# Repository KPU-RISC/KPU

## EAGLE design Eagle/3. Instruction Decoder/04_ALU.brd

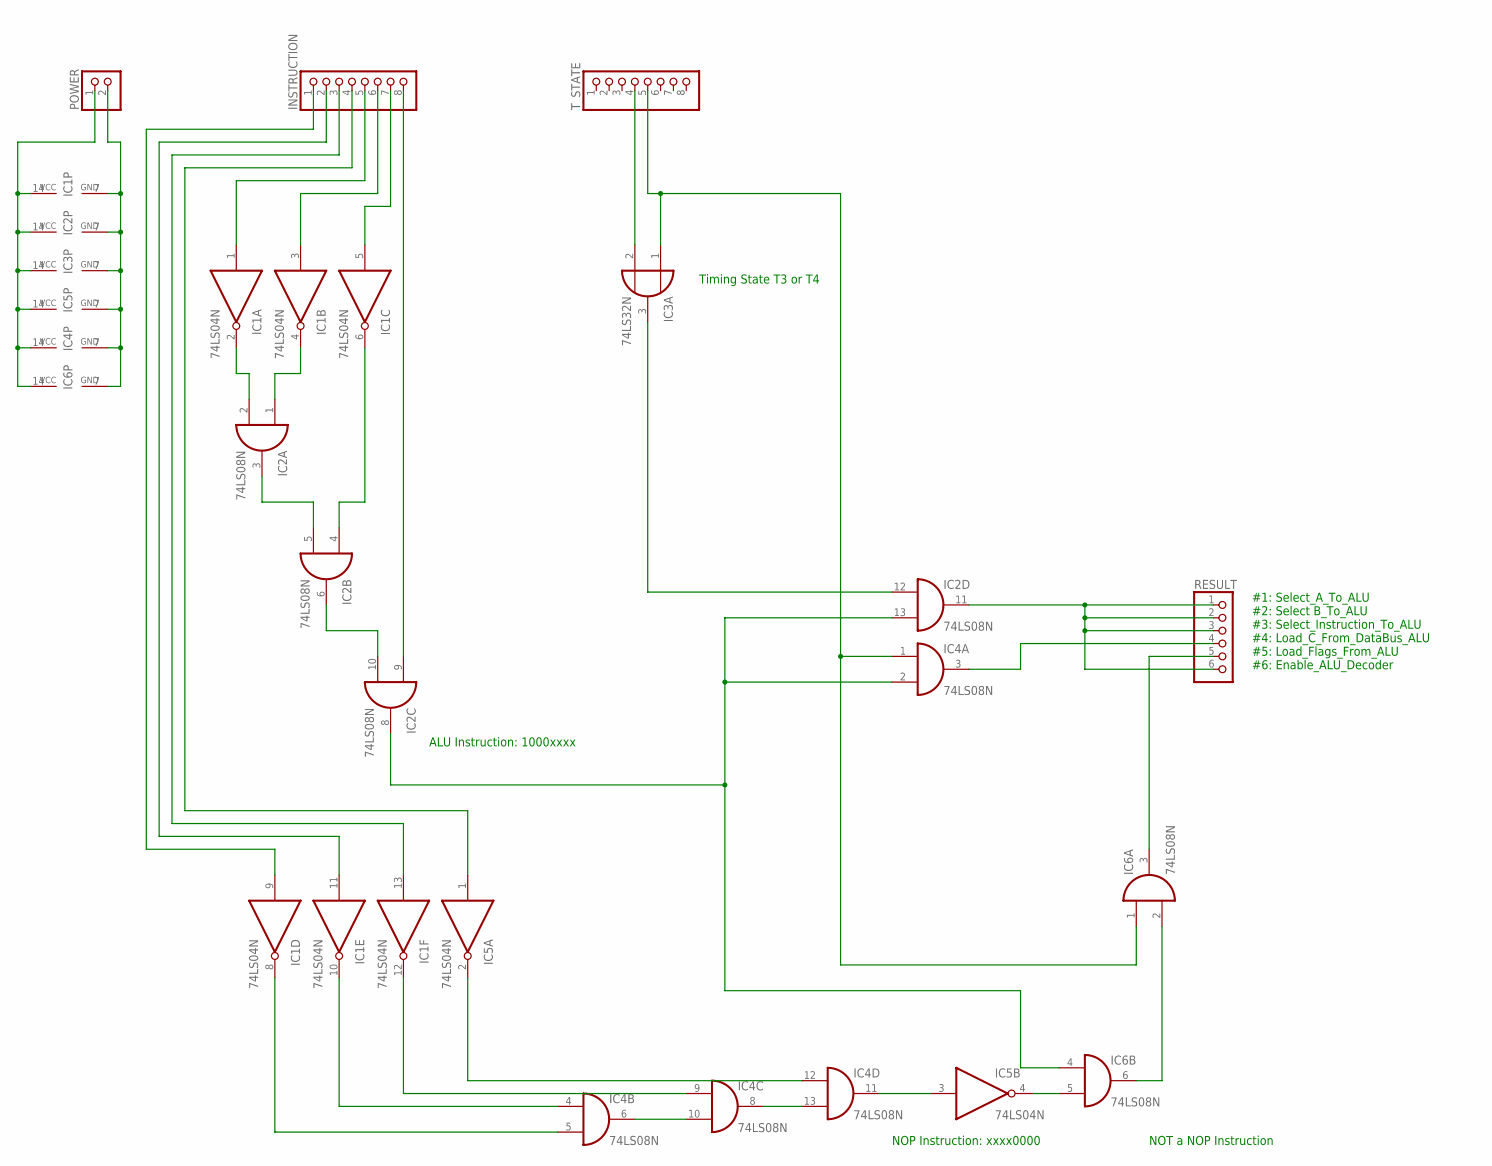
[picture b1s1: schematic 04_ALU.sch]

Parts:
IC1, IC5: 74LS04N; DIL14
IC2, IC4, IC6: 74LS08N; DIL14
IC3: 74LS32N; DIL14
INSTRUCTION: PINHD-1X8; 1X08
POWER: PINHD-1X2; 1X02
RESULT: PINHD-1X6; 1X06
T_STATE: PINHD-1X8; 1X08

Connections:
GND: IC1.7 (GND), IC2.7 (GND), IC3.7 (GND), IC4.7 (GND), IC5.7 (GND), IC6.7 (GND), POWER.2
unnamed: IC1.1 (I), INSTRUCTION.5
unnamed: IC1.3 (I), INSTRUCTION.6
unnamed: IC1.5 (I), INSTRUCTION.7
unnamed: IC1.2 (O), IC2.2 (I1)
unnamed: IC1.4 (O), IC2.1 (I0)
unnamed: IC2.3 (O), IC2.5 (I1)
unnamed: IC1.6 (O), IC2.4 (I0)
unnamed: IC2.9 (I0), INSTRUCTION.8
unnamed: IC2.6 (O), IC2.10 (I1)
unnamed: IC3.2 (I1), T_STATE.4
unnamed: IC3.1 (I0), IC4.1 (I0), IC6.1 (I0), T_STATE.5
unnamed: IC2.8 (O), IC2.13 (I1), IC4.2 (I1), IC6.4 (I0)
unnamed: IC2.12 (I0), IC3.3 (O)
unnamed: IC2.11 (O), RESULT.1, RESULT.2, RESULT.3, RESULT.6
unnamed: IC4.3 (O), RESULT.4
unnamed: IC1.9 (I), INSTRUCTION.1
unnamed: IC1.11 (I), INSTRUCTION.2
unnamed: IC1.13 (I), INSTRUCTION.3
unnamed: IC5.1 (I), INSTRUCTION.4
unnamed: IC1.8 (O), IC4.5 (I1)
unnamed: IC1.10 (O), IC4.4 (I0)
unnamed: IC4.6 (O), IC4.10 (I1)
unnamed: IC1.12 (O), IC4.9 (I0)
unnamed: IC4.8 (O), IC4.13 (I1)
unnamed: IC4.12 (I0), IC5.2 (O)
unnamed: IC4.11 (O), IC5.3 (I)
unnamed: IC5.4 (O), IC6.5 (I1)
unnamed: IC6.3 (O), RESULT.5
unnamed: IC6.2 (I1), IC6.6 (O)
VCC: IC1.14 (VCC), IC2.14 (VCC), IC3.14 (VCC), IC4.14 (VCC), IC5.14 (VCC), IC6.14 (VCC), POWER.1

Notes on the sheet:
ALU Instruction: 1000xxxx
Timing State T3 or T4
#1: Select_A_To_ALU #2: Select B_To_ALU #3: Select_Instruction_To_ALU #4: Load_C_From_DataBus_ALU #5: Load_Flags_From_ALU #6: Enable_ALU_Decoder
NOP Instruction: xxxx0000
NOT a NOP Instruction

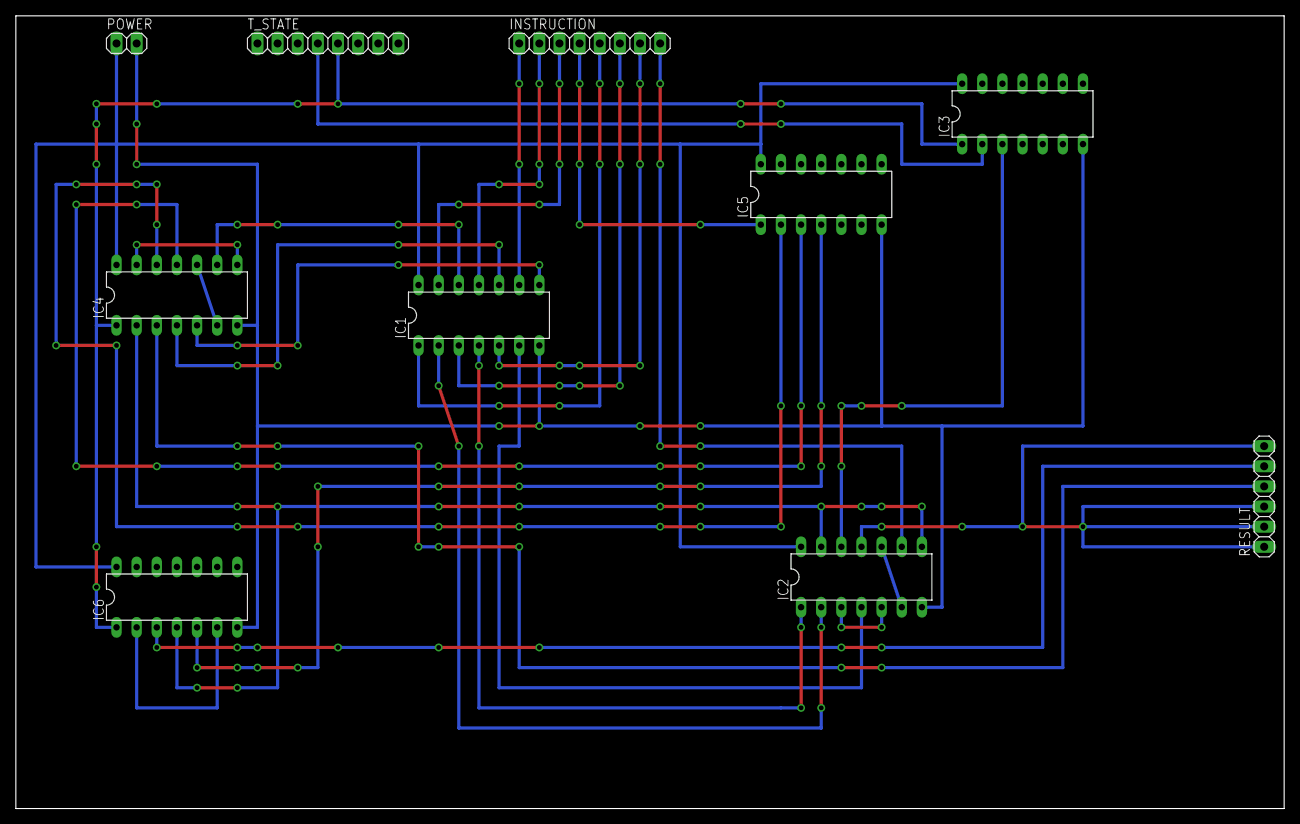
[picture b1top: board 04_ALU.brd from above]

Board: 2 copper layers, 160.0 x 100.0 mm, 10 parts (0 on the bottom side), 31 nets.

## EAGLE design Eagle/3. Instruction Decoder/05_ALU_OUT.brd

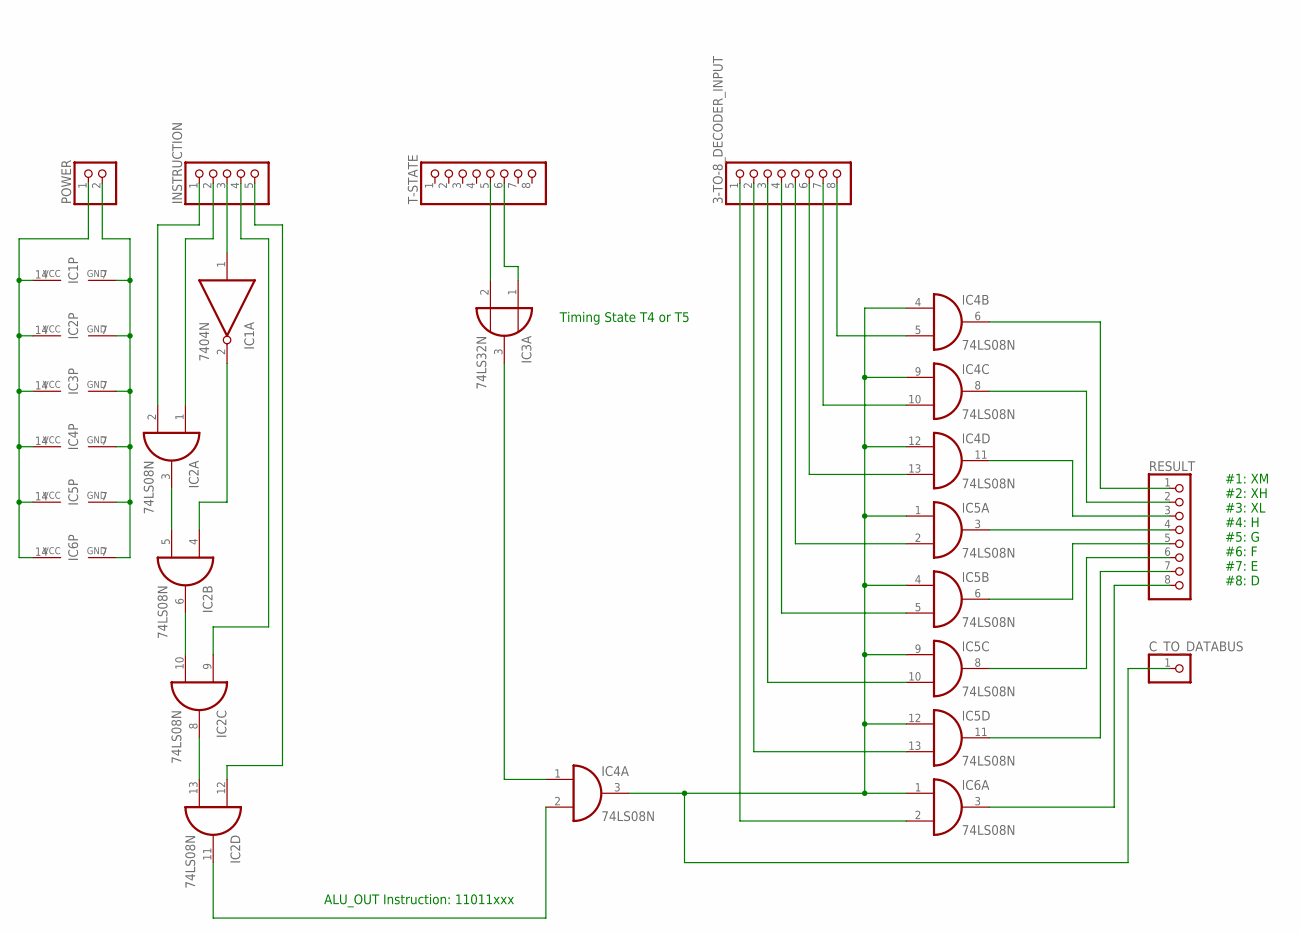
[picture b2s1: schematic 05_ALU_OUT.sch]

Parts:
3-TO-8_DECODER_INPUT: PINHD-1X8; 1X08
C_TO_DATABUS: PINHD-1X1; 1X01
IC1: 7404N; DIL14
IC2, IC4, IC5, IC6: 74LS08N; DIL14
IC3: 74LS32N; DIL14
INSTRUCTION: PINHD-1X5; 1X05
POWER: PINHD-1X2; 1X02
RESULT: PINHD-1X8; 1X08
T-STATE: PINHD-1X8; 1X08

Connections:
GND: IC1.7 (GND), IC2.7 (GND), IC3.7 (GND), IC4.7 (GND), IC5.7 (GND), IC6.7 (GND), POWER.2
unnamed: IC1.1 (I), INSTRUCTION.3
unnamed: IC2.2 (I1), INSTRUCTION.1
unnamed: IC2.1 (I0), INSTRUCTION.2
unnamed: IC2.3 (O), IC2.5 (I1)
unnamed: IC1.2 (O), IC2.4 (I0)
unnamed: IC2.6 (O), IC2.10 (I1)
unnamed: IC2.9 (I0), INSTRUCTION.4
unnamed: IC2.8 (O), IC2.13 (I1)
unnamed: IC2.12 (I0), INSTRUCTION.5
unnamed: IC2.11 (O), IC4.2 (I1)
unnamed: IC3.2 (I1), T-STATE.5
unnamed: IC3.1 (I0), T-STATE.6
unnamed: IC3.3 (O), IC4.1 (I0)
unnamed: C_TO_DATABUS.1, IC4.3 (O), IC4.4 (I0), IC4.9 (I0), IC4.12 (I0), IC5.1 (I0), IC5.4 (I0), IC5.9 (I0), IC5.12 (I0), IC6.1 (I0)
unnamed: 3-TO-8_DECODER_INPUT.8, IC4.5 (I1)
unnamed: 3-TO-8_DECODER_INPUT.7, IC4.10 (I1)
unnamed: 3-TO-8_DECODER_INPUT.6, IC4.13 (I1)
unnamed: 3-TO-8_DECODER_INPUT.5, IC5.2 (I1)
unnamed: 3-TO-8_DECODER_INPUT.4, IC5.5 (I1)
unnamed: 3-TO-8_DECODER_INPUT.3, IC5.10 (I1)
unnamed: 3-TO-8_DECODER_INPUT.2, IC5.13 (I1)
unnamed: 3-TO-8_DECODER_INPUT.1, IC6.2 (I1)
unnamed: IC4.6 (O), RESULT.1
unnamed: IC4.8 (O), RESULT.2
unnamed: IC4.11 (O), RESULT.3
unnamed: IC5.3 (O), RESULT.4
unnamed: IC5.6 (O), RESULT.5
unnamed: IC5.8 (O), RESULT.6
unnamed: IC5.11 (O), RESULT.7
unnamed: IC6.3 (O), RESULT.8
VCC: IC1.14 (VCC), IC2.14 (VCC), IC3.14 (VCC), IC4.14 (VCC), IC5.14 (VCC), IC6.14 (VCC), POWER.1

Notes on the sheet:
ALU_OUT Instruction: 11011xxx
Timing State T4 or T5
#1: XM #2: XH #3: XL #4: H #5: G #6: F #7: E #8: D

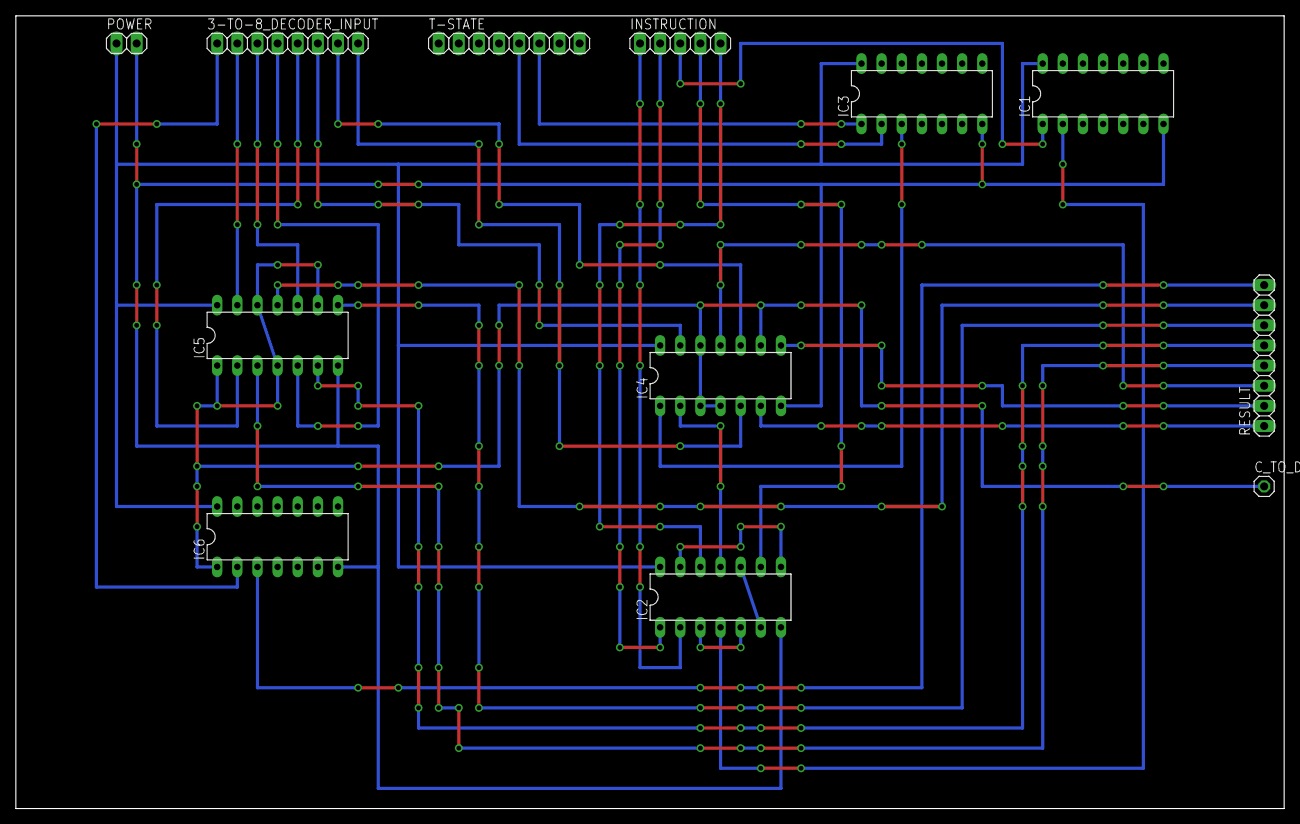
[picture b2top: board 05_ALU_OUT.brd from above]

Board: 2 copper layers, 160.0 x 100.0 mm, 12 parts (0 on the bottom side), 32 nets.

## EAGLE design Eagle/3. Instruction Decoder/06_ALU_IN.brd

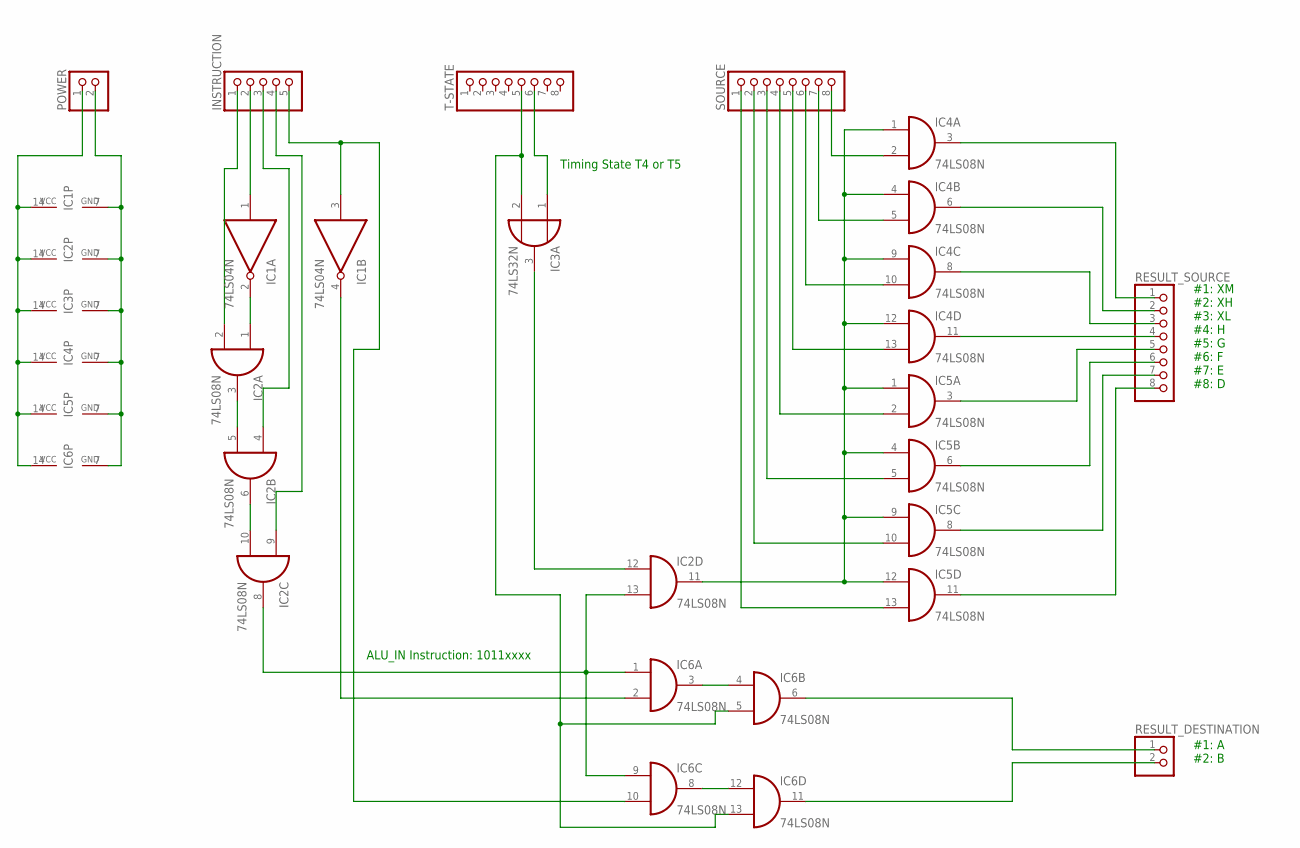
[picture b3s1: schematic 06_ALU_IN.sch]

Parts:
IC1: 74LS04N; DIL14
IC2, IC4, IC5, IC6: 74LS08N; DIL14
IC3: 74LS32N; DIL14
INSTRUCTION: PINHD-1X5; 1X05
POWER: PINHD-1X2; 1X02
RESULT_DESTINATION: PINHD-1X2; 1X02
RESULT_SOURCE: PINHD-1X8; 1X08
SOURCE: PINHD-1X8; 1X08
T-STATE: PINHD-1X8; 1X08

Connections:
GND: IC1.7 (GND), IC2.7 (GND), IC3.7 (GND), IC4.7 (GND), IC5.7 (GND), IC6.7 (GND), POWER.2
unnamed: IC1.1 (I), INSTRUCTION.2
unnamed: IC2.2 (I1), INSTRUCTION.1
unnamed: IC4.3 (O), RESULT_SOURCE.1
unnamed: IC1.2 (O), IC2.1 (I0)
unnamed: IC2.3 (O), IC2.5 (I1)
unnamed: IC2.4 (I0), INSTRUCTION.3
unnamed: IC2.6 (O), IC2.10 (I1)
unnamed: IC2.9 (I0), INSTRUCTION.4
unnamed: IC2.8 (O), IC2.13 (I1), IC6.1 (I0), IC6.9 (I0)
unnamed: IC3.2 (I1), IC6.5 (I1), IC6.13 (I1), T-STATE.5
unnamed: IC3.1 (I0), T-STATE.6
unnamed: IC2.12 (I0), IC3.3 (O)
unnamed: IC2.11 (O), IC4.1 (I0), IC4.4 (I0), IC4.9 (I0), IC4.12 (I0), IC5.1 (I0), IC5.4 (I0), IC5.9 (I0), IC5.12 (I0)
unnamed: IC5.13 (I1), SOURCE.1
unnamed: IC5.10 (I1), SOURCE.2
unnamed: IC5.5 (I1), SOURCE.3
unnamed: IC5.2 (I1), SOURCE.4
unnamed: IC4.13 (I1), SOURCE.5
unnamed: IC4.10 (I1), SOURCE.6
unnamed: IC4.5 (I1), SOURCE.7
unnamed: IC4.2 (I1), SOURCE.8
unnamed: IC4.6 (O), RESULT_SOURCE.2
unnamed: IC4.8 (O), RESULT_SOURCE.3
unnamed: IC4.11 (O), RESULT_SOURCE.4
unnamed: IC5.3 (O), RESULT_SOURCE.5
unnamed: IC5.6 (O), RESULT_SOURCE.6
unnamed: IC5.8 (O), RESULT_SOURCE.7
unnamed: IC5.11 (O), RESULT_SOURCE.8
unnamed: IC1.3 (I), IC6.10 (I1), INSTRUCTION.5
unnamed: IC1.4 (O), IC6.2 (I1)
unnamed: IC6.3 (O), IC6.4 (I0)
unnamed: IC6.8 (O), IC6.12 (I0)
unnamed: IC6.6 (O), RESULT_DESTINATION.1
unnamed: IC6.11 (O), RESULT_DESTINATION.2
VCC: IC1.14 (VCC), IC2.14 (VCC), IC3.14 (VCC), IC4.14 (VCC), IC5.14 (VCC), IC6.14 (VCC), POWER.1

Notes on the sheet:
ALU_IN Instruction: 1011xxxx
Timing State T4 or T5
#1: XM #2: XH #3: XL #4: H #5: G #6: F #7: E #8: D
#1: A #2: B

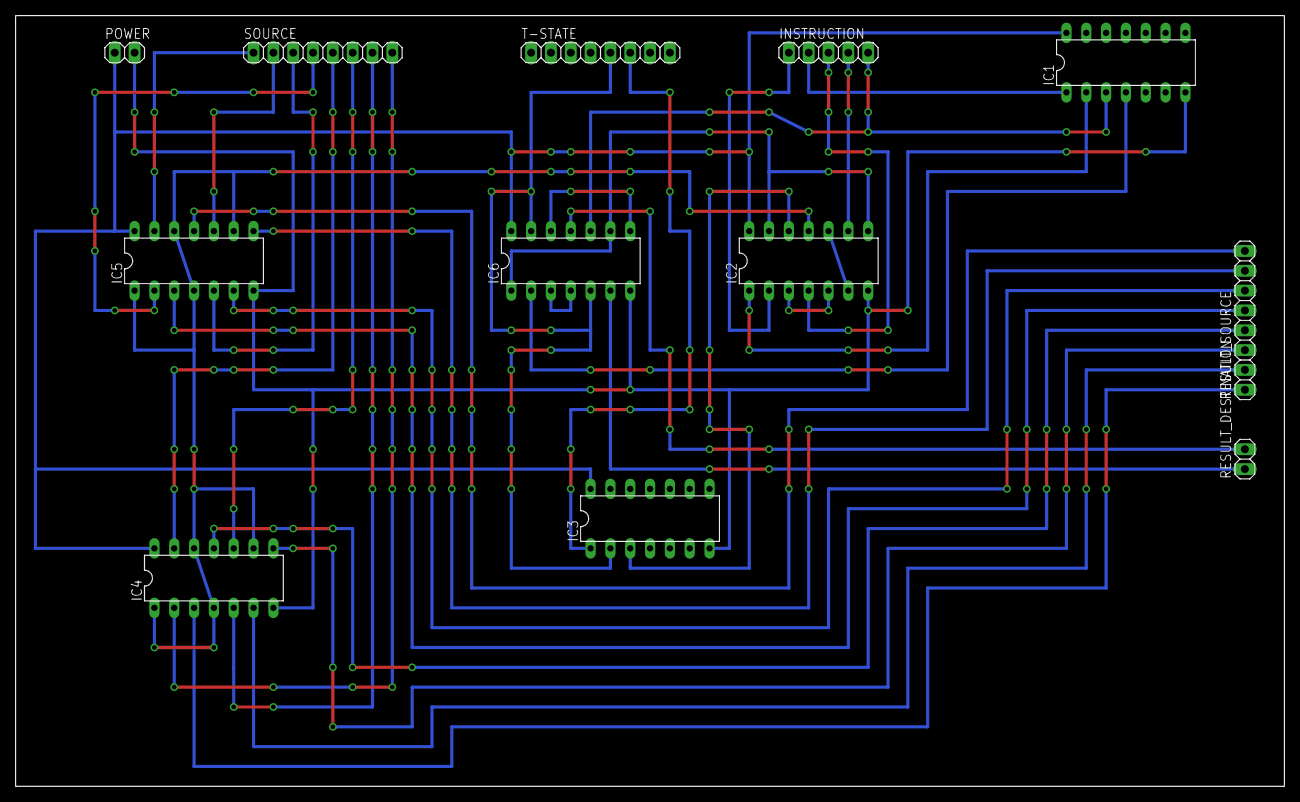
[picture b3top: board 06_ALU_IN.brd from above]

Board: 2 copper layers, 162.5 x 98.7 mm, 12 parts (0 on the bottom side), 36 nets.

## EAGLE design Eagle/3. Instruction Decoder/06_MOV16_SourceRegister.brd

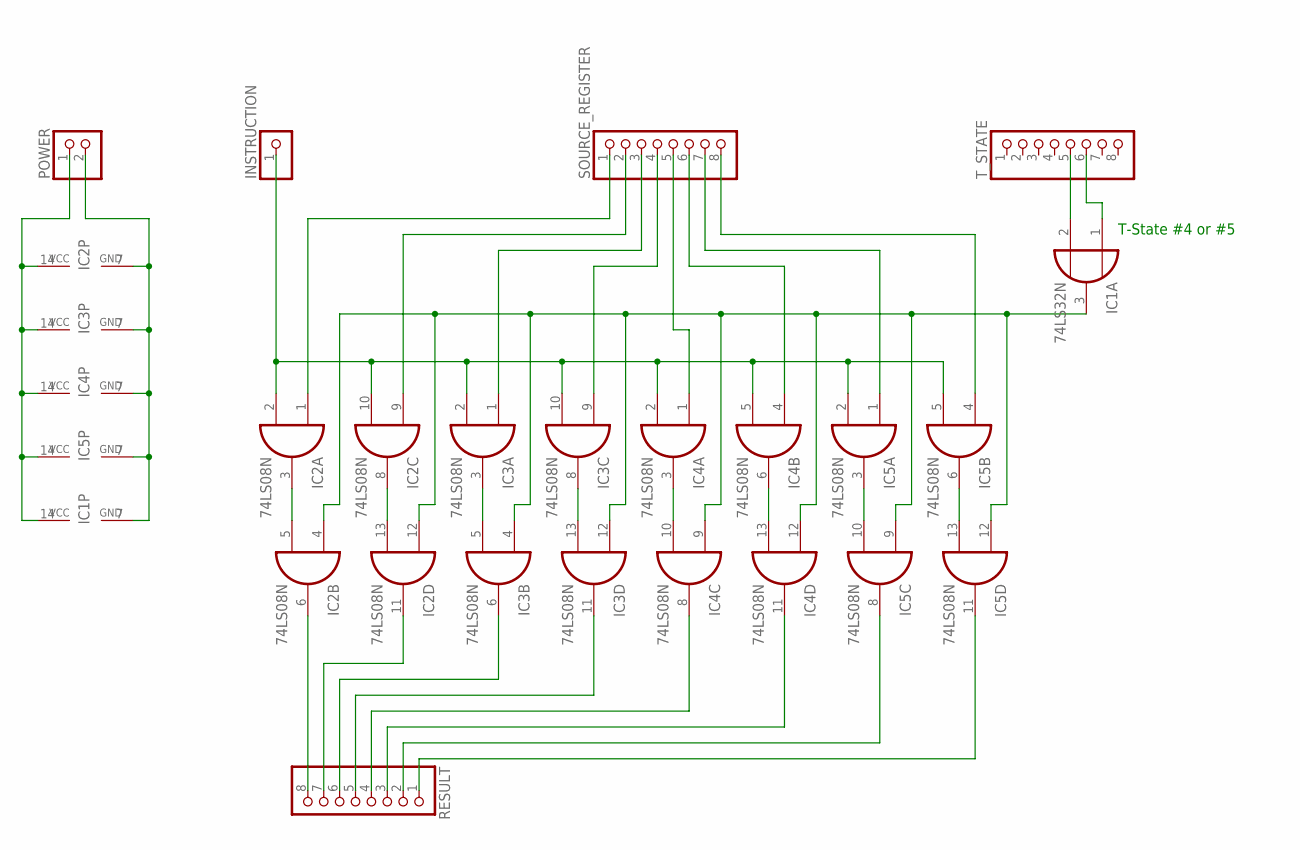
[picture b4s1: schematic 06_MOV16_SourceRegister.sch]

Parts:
IC1: 74LS32N; DIL14
IC2, IC3, IC4, IC5: 74LS08N; DIL14
INSTRUCTION: PINHD-1X1; 1X01
POWER: PINHD-1X2; 1X02
RESULT: PINHD-1X8; 1X08
SOURCE_REGISTER: PINHD-1X8; 1X08
T_STATE: PINHD-1X8; 1X08

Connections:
GND: IC1.7 (GND), IC2.7 (GND), IC3.7 (GND), IC4.7 (GND), IC5.7 (GND), POWER.2
unnamed: IC1.2 (I1), T_STATE.5
unnamed: IC1.1 (I0), T_STATE.6
unnamed: IC2.2 (I1), IC2.10 (I1), IC3.2 (I1), IC3.10 (I1), IC4.2 (I1), IC4.5 (I1), IC5.2 (I1), IC5.5 (I1), INSTRUCTION.1
unnamed: IC2.1 (I0), SOURCE_REGISTER.1
unnamed: IC2.3 (O), IC2.5 (I1)
unnamed: IC1.3 (O), IC2.4 (I0), IC2.12 (I0), IC3.4 (I0), IC3.12 (I0), IC4.9 (I0), IC4.12 (I0), IC5.9 (I0), IC5.12 (I0)
unnamed: IC2.6 (O), RESULT.8
unnamed: IC2.9 (I0), SOURCE_REGISTER.2
unnamed: IC2.8 (O), IC2.13 (I1)
unnamed: IC3.1 (I0), SOURCE_REGISTER.3
unnamed: IC2.11 (O), RESULT.7
unnamed: IC3.3 (O), IC3.5 (I1)
unnamed: IC3.6 (O), RESULT.6
unnamed: IC3.9 (I0), SOURCE_REGISTER.4
unnamed: IC3.8 (O), IC3.13 (I1)
unnamed: IC3.11 (O), RESULT.5
unnamed: IC4.1 (I0), SOURCE_REGISTER.5
unnamed: IC4.3 (O), IC4.10 (I1)
unnamed: IC4.8 (O), RESULT.4
unnamed: IC4.4 (I0), SOURCE_REGISTER.6
unnamed: IC4.6 (O), IC4.13 (I1)
unnamed: IC4.11 (O), RESULT.3
unnamed: IC5.1 (I0), SOURCE_REGISTER.7
unnamed: IC5.3 (O), IC5.10 (I1)
unnamed: IC5.8 (O), RESULT.2
unnamed: IC5.4 (I0), SOURCE_REGISTER.8
unnamed: IC5.6 (O), IC5.13 (I1)
unnamed: IC5.11 (O), RESULT.1
VCC: IC1.14 (VCC), IC2.14 (VCC), IC3.14 (VCC), IC4.14 (VCC), IC5.14 (VCC), POWER.1

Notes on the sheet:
T-State #4 or #5

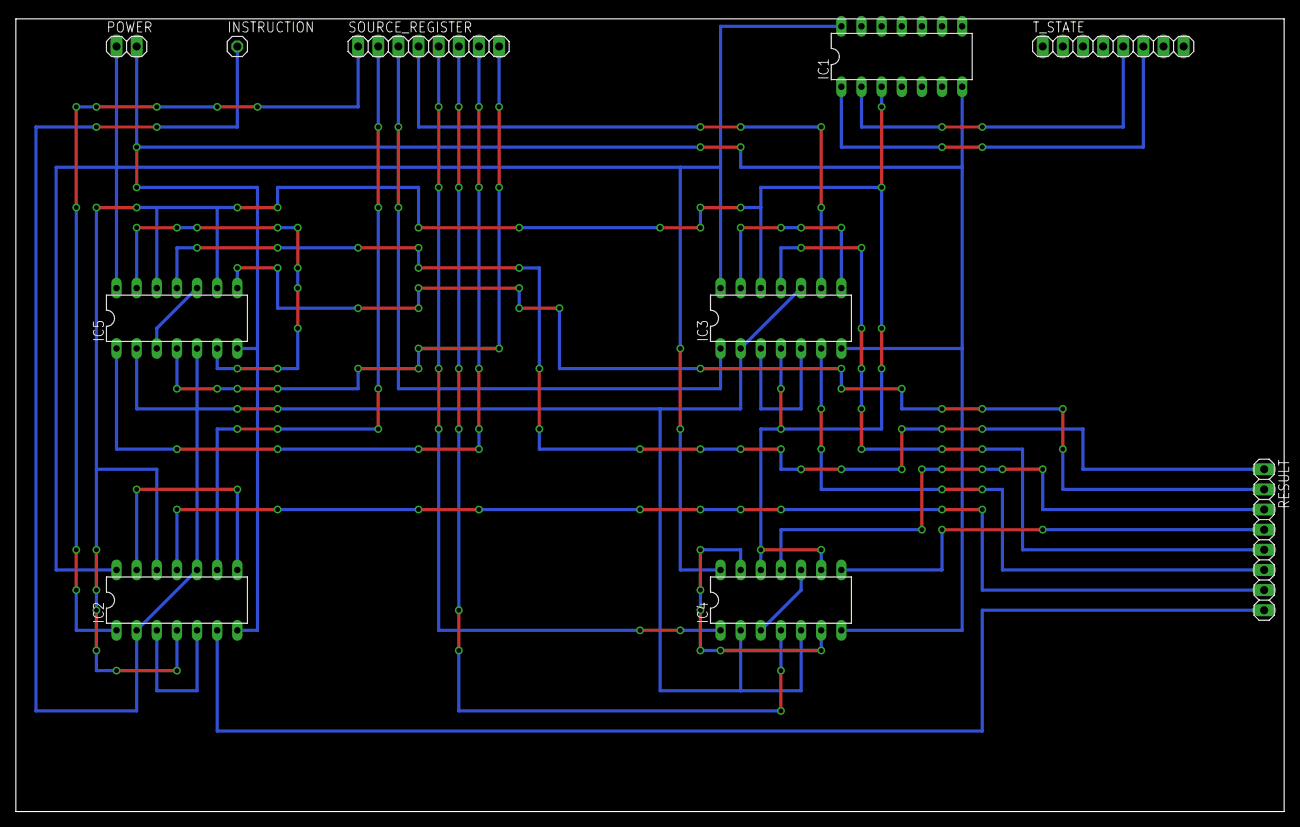
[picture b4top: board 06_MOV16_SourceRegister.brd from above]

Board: 2 copper layers, 160.0 x 100.0 mm, 10 parts (0 on the bottom side), 30 nets.

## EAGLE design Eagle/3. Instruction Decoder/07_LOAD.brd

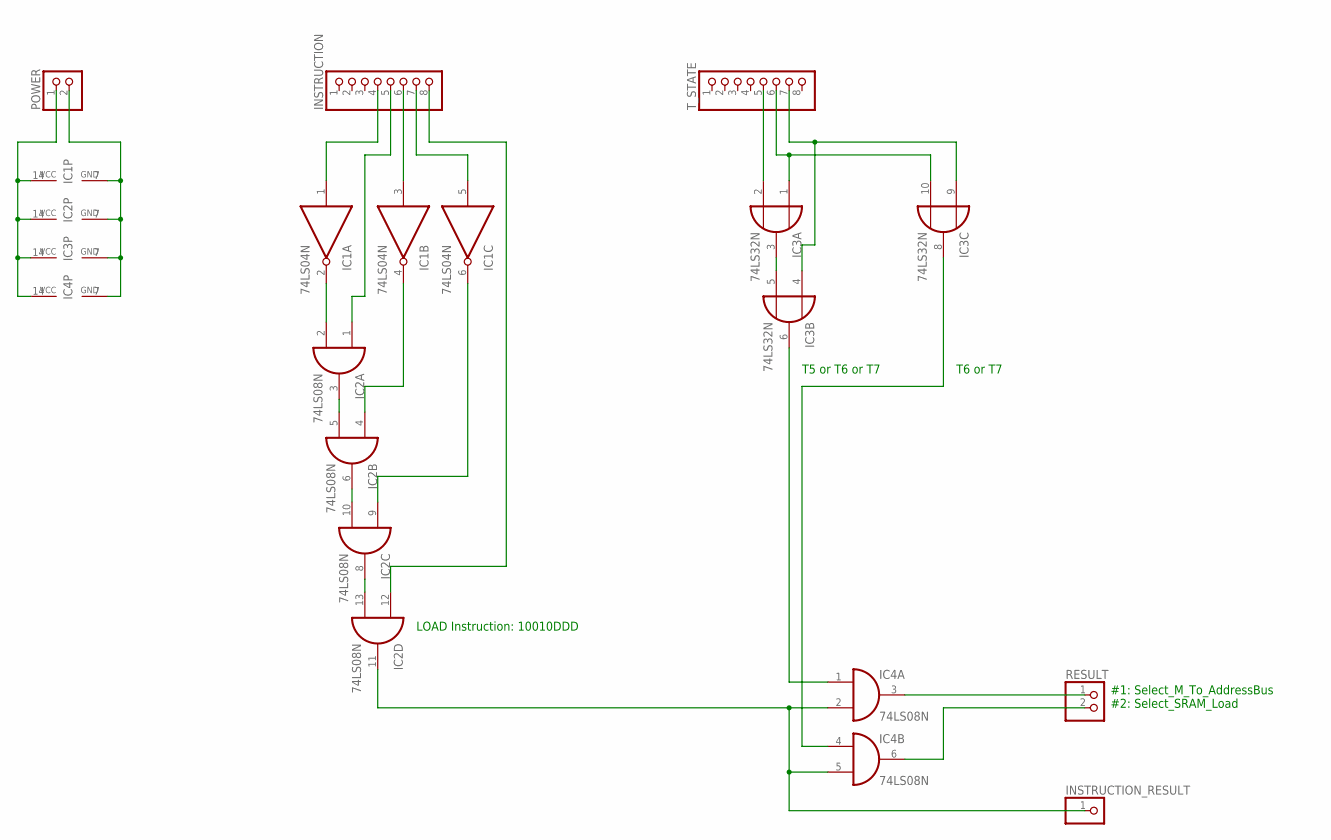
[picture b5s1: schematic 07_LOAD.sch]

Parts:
IC1: 74LS04N; DIL14
IC2, IC4: 74LS08N; DIL14
IC3: 74LS32N; DIL14
INSTRUCTION: PINHD-1X8; 1X08
INSTRUCTION_RESULT: PINHD-1X1; 1X01
POWER: PINHD-1X2; 1X02
RESULT: PINHD-1X2; 1X02
T_STATE: PINHD-1X8; 1X08

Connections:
GND: IC1.7 (GND), IC2.7 (GND), IC3.7 (GND), IC4.7 (GND), POWER.2
unnamed: IC1.1 (I), INSTRUCTION.4
unnamed: IC1.3 (I), INSTRUCTION.6
unnamed: IC1.5 (I), INSTRUCTION.7
unnamed: IC1.2 (O), IC2.2 (I1)
unnamed: IC2.1 (I0), INSTRUCTION.5
unnamed: IC2.3 (O), IC2.5 (I1)
unnamed: IC1.4 (O), IC2.4 (I0)
unnamed: IC2.6 (O), IC2.10 (I1)
unnamed: IC1.6 (O), IC2.9 (I0)
unnamed: IC2.8 (O), IC2.13 (I1)
unnamed: IC2.12 (I0), INSTRUCTION.8
unnamed: IC3.2 (I1), T_STATE.5
unnamed: IC3.1 (I0), IC3.10 (I1), T_STATE.6
unnamed: IC3.3 (O), IC3.5 (I1)
unnamed: IC2.11 (O), IC4.2 (I1), IC4.5 (I1), INSTRUCTION_RESULT.1
unnamed: IC3.6 (O), IC4.1 (I0)
unnamed: IC3.8 (O), IC4.4 (I0)
unnamed: IC4.6 (O), RESULT.2
unnamed: IC3.4 (I0), IC3.9 (I0), T_STATE.7
RESULT: IC4.3 (O), RESULT.1
VCC: IC1.14 (VCC), IC2.14 (VCC), IC3.14 (VCC), IC4.14 (VCC), POWER.1

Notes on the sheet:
LOAD Instruction: 10010DDD
T5 or T6 or T7
T6 or T7
#1: Select_M_To_AddressBus #2: Select_SRAM_Load

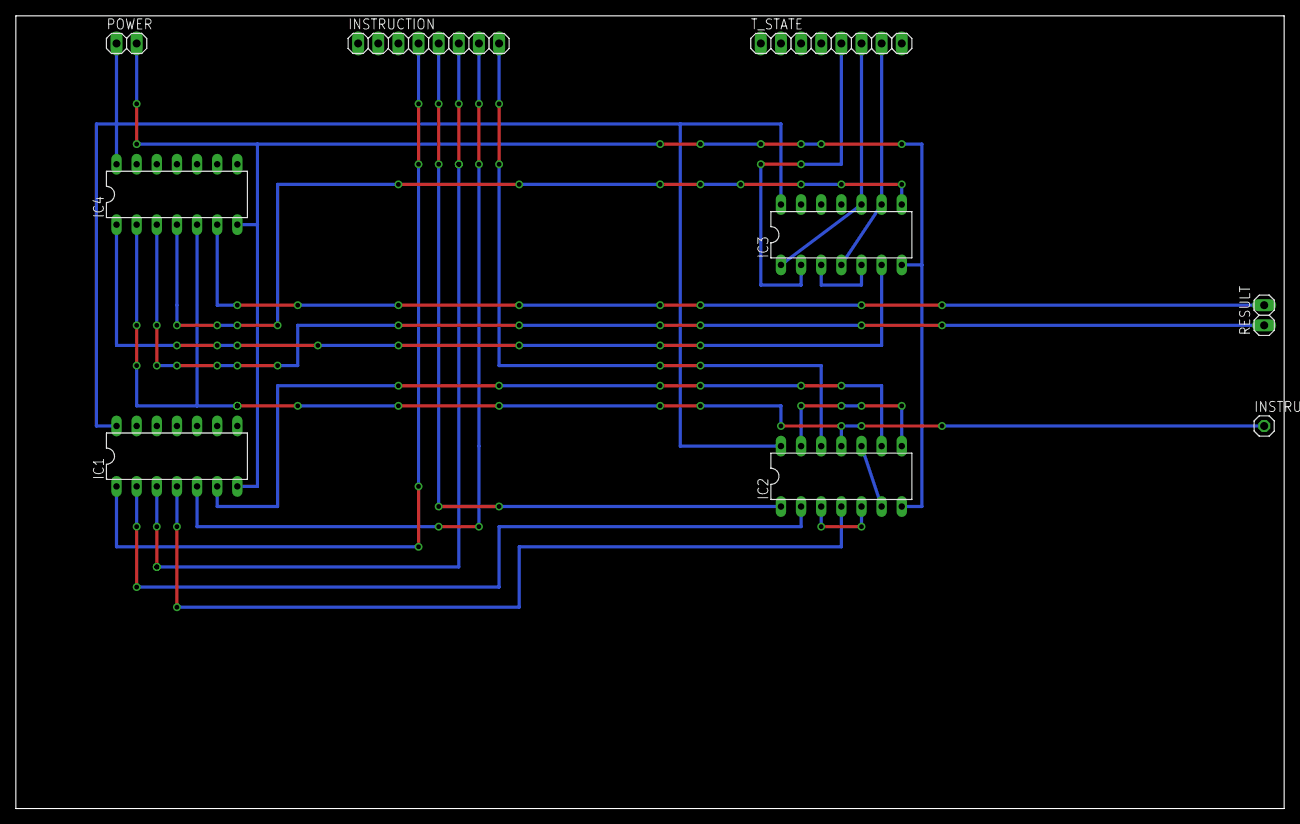
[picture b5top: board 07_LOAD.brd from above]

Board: 2 copper layers, 160.0 x 100.0 mm, 9 parts (0 on the bottom side), 22 nets.

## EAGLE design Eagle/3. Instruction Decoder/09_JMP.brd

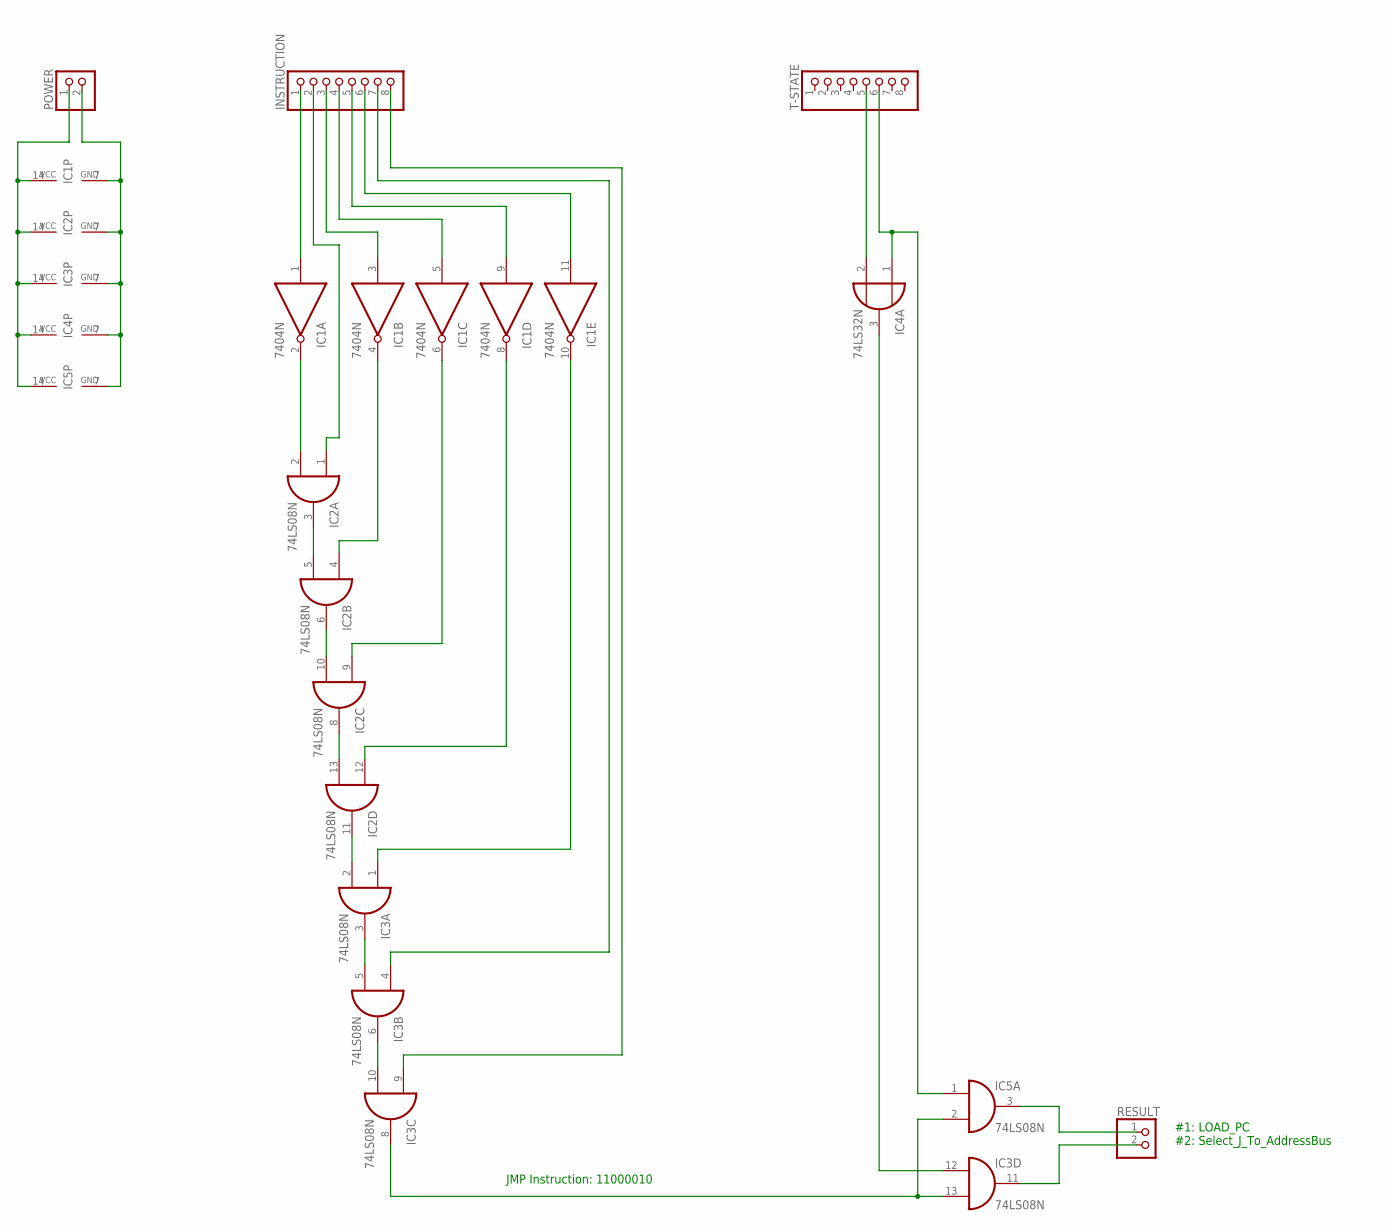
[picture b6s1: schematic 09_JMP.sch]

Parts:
IC1: 7404N; DIL14
IC2, IC3, IC5: 74LS08N; DIL14
IC4: 74LS32N; DIL14
INSTRUCTION: PINHD-1X8; 1X08
POWER: PINHD-1X2; 1X02
RESULT: PINHD-1X2; 1X02
T-STATE: PINHD-1X8; 1X08

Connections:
GND: IC1.7 (GND), IC2.7 (GND), IC3.7 (GND), IC4.7 (GND), IC5.7 (GND), POWER.2
unnamed: IC1.1 (I), INSTRUCTION.1
unnamed: IC2.1 (I0), INSTRUCTION.2
unnamed: IC1.3 (I), INSTRUCTION.3
unnamed: IC1.5 (I), INSTRUCTION.4
unnamed: IC1.9 (I), INSTRUCTION.5
unnamed: IC1.11 (I), INSTRUCTION.6
unnamed: IC3.4 (I0), INSTRUCTION.7
unnamed: IC3.9 (I0), INSTRUCTION.8
unnamed: IC1.4 (O), IC2.4 (I0)
unnamed: IC1.2 (O), IC2.2 (I1)
unnamed: IC1.6 (O), IC2.9 (I0)
unnamed: IC1.8 (O), IC2.12 (I0)
unnamed: IC1.10 (O), IC3.1 (I0)
unnamed: IC2.3 (O), IC2.5 (I1)
unnamed: IC4.2 (I1), T-STATE.5
unnamed: IC2.6 (O), IC2.10 (I1)
unnamed: IC4.1 (I0), IC5.1 (I0), T-STATE.6
unnamed: IC2.8 (O), IC2.13 (I1)
unnamed: IC3.12 (I0), IC4.3 (O)
unnamed: IC2.11 (O), IC3.2 (I1)
unnamed: IC3.3 (O), IC3.5 (I1)
unnamed: IC3.6 (O), IC3.10 (I1)
unnamed: IC5.3 (O), RESULT.1
unnamed: IC3.11 (O), RESULT.2
unnamed: IC3.8 (O), IC3.13 (I1), IC5.2 (I1)
VCC: IC1.14 (VCC), IC2.14 (VCC), IC3.14 (VCC), IC4.14 (VCC), IC5.14 (VCC), POWER.1

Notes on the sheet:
JMP Instruction: 11000010
#1: LOAD_PC #2: Select_J_To_AddressBus

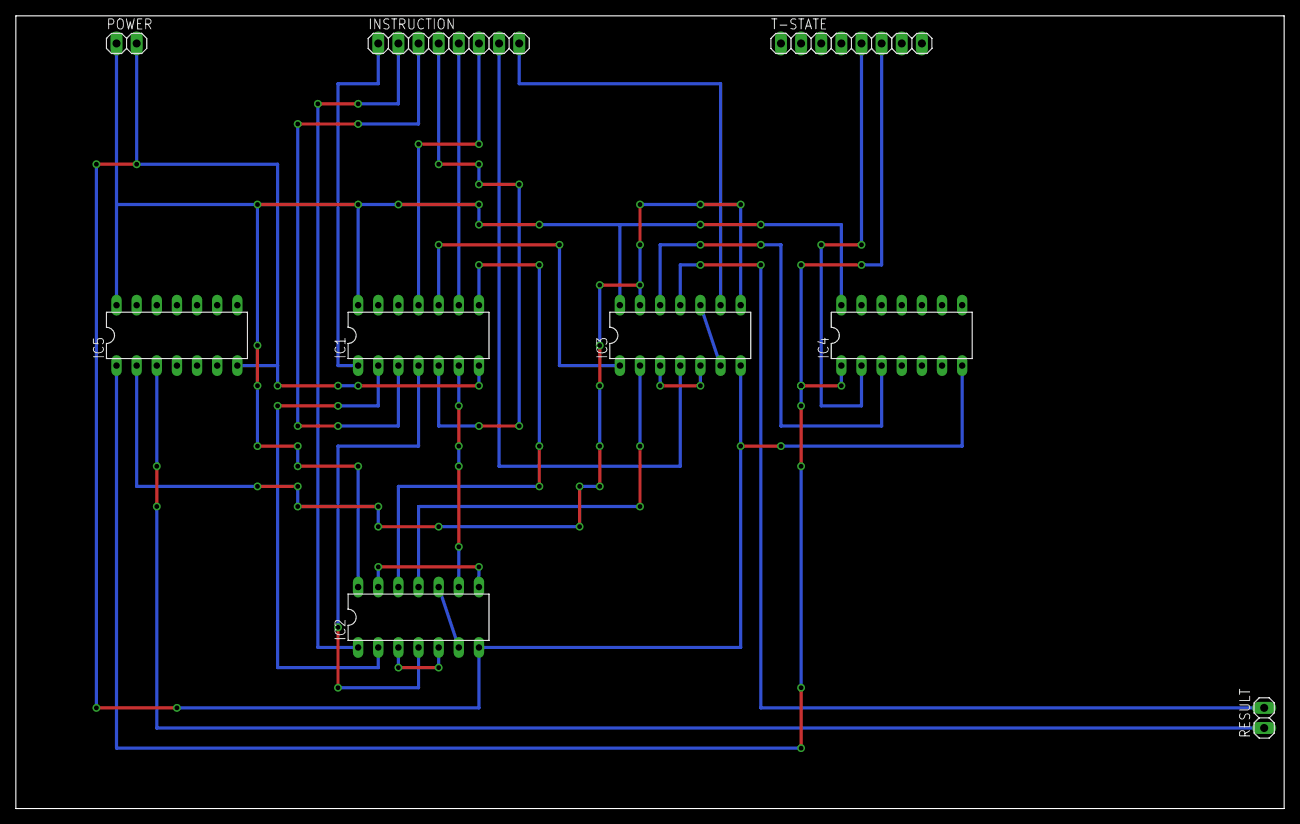
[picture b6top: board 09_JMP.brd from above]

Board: 2 copper layers, 160.0 x 100.0 mm, 9 parts (0 on the bottom side), 27 nets.
